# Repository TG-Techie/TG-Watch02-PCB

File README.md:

# TG-Watch02-PCB
---

## Description
Why buy an apple watch when you can spend your weekends building a microcontroller based "smart" watch instead? the TG-Watch is an open source, not-dumb watch meant for makers who want to hack on their watch or as great starting point to learn about programming.

Some of its features include:
- a 240x240, 1.54" lcd
- capacitive touchscreen
- USB Type-C port (2.0)
- Step counter and pedometer
- vibration motor and haptic motor driver
- Bluetooth 5, Bluetooth mesh, Thread, ZigBee

## Software
The TG-Watch was designed to run circuitpython, this gives anyone the flexibility to run what they can write. Additionally, there is on-going development for a python GUI framework (TG-Gui-4 and TG-Gui 5) that runs on the watch. This framework is intended to make writing UI programs to run on the fun and approachable. (Currently under going a re-write)

## Examples
Updates about software and hardware are often posted to twitter, [here](https://twitter.com/TG_Techie).

## What's on it?
- 2295018-2, USB Type-C Connector
- LSM6DSOX, accel & gyro
- DRV2605, Haptic motor driver
- NRF52840, MCU and BLE IC
- BQ27441, battery charge tracker IC
- DS3231, real time clock

## Contribution and Questions
If you have any questions feel free to reach out and start a discussion on twitter at `@TG_Techie` or on discord at `@TG-Techie#5402`.

## License

Design and copyright by Jonah Yolles-Murphy, 2020

Creative Commons Attribution/Share-Alike, all text above must be included in any redistribution. See license.txt for additional details.

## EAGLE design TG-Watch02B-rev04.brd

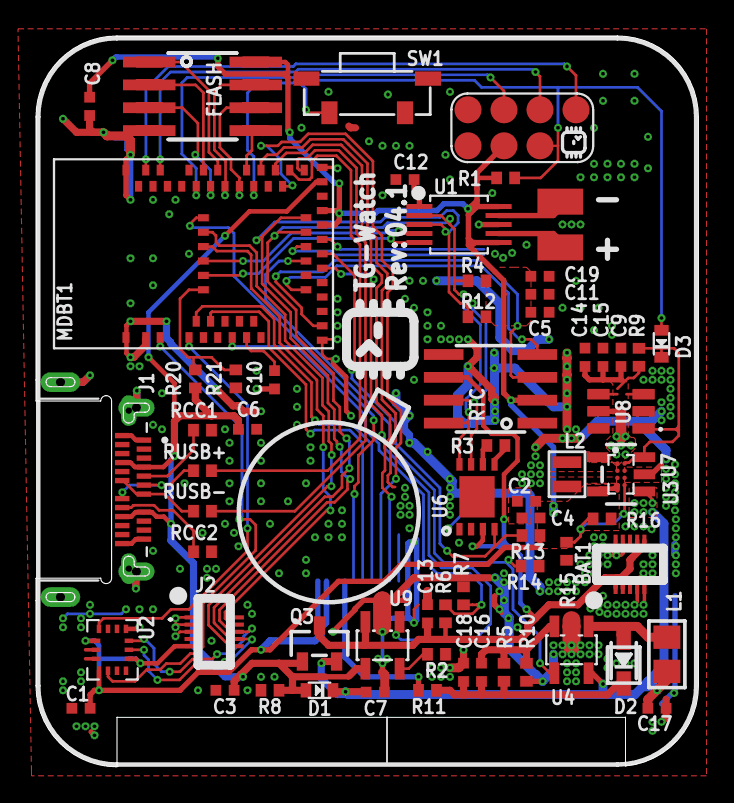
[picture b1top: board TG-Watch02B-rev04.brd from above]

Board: 2 copper layers, 36.8 x 40.6 mm, 66 parts (0 on the bottom side), 56 nets.

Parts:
04.1: TG-Watch; TG-PROD-LABEL-5MM
C1, C18: 4.7uf; MICROBUILDER__0402_NODIMS
C2, C3, C4, C5, C6, C7, C8, C9, C13, C14, C15, C17, C19: 10uf; MICROBUILDER__0402_NODIMS
C10: 0.1uF; MICROBUILDER__0402_NODIMS
C11, C12: 1uf; MICROBUILDER__0402_NODIMS
C16: 0.1nF; MICROBUILDER__0402_NODIMS
D1: NSR05T40XV2; SOD-523
D2: BAT54T1G; SOD-323
D3: BAS16XV2T1G; SOD-523
FLASH: W25Q128JVSIQ TR; SOIC8_208MIL
HEDR2: 1X02SMD; 1X2_SMD
IC3: W25Q128JVSIQ TR; SOIC8_150MIL
J1: USB-C-CON-TG_MOD-2295018-2.0; TG_RM_TE_2295018-2
J2: DISP_1.54_LCMTF15423A-C_LCD+CAPTCH_ASSEMBLY_DUALS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; TF-LCM15423A-C_DUALSIDE
J3: CON-BAT-TG-MEZ_FEMALE; MEZ-DF37NC-10DS
L1: 10uH; 0805
L2: 1uH - HMLQ20161B-1R0MDR; NONSTANDARD_INDUCTOR_5
MDBT1: MDBT50
Q3: DMG2305; SOT23-R
R1, R10, R13, R14: 10k; TG_0402
R2: 2k; TG_0402
R3: 11k; TG_0402
R4, R9, R12, R21: 100k; TG_0402
R5: 68k; TG_0402
R6: 270k; TG_0402
R7, R16: 330k; TG_0402
R8: 2.7K; TG_0402
R11: 220R; TG_0402
R15: 59k; TG_0402
R20: 51k; TG_0402
RCC1, RCC2: 5.1k; TG_0402
RTC: SEN-TIME-DS3231-(PERSICION-TEMP); SOIC8_150MIL
RUSB+: 22ohm; TG_0402
RUSB-: 22ohm; TG_0402
SW1: MICROBUILDER_SPST_TACTILE_RA_NO_ALIGN
U1: MICROBUILDER_PSOP10
U2: MICROBUILDER_LSM6DSOX; MICROBUILDER_LGA-14L
U3: VREG-TPS63036; TPS63036YFGR_BGA8N40P4X2_NOSILK
U4: FAN5331SX; SOT23-5@1
U5: MCP73831/OT; SOT23-5L
U6: LC709203F; WDFN8_3X4_0.65
U7: SOT23-5
U8: UNDERVOLT-TPS3702CX3; SOT95P280X110-6N
U$3: CON_SWD_POGO; SWD_POGO

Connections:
3V3: C1.2, C2.2, C4.2, C5.2, C8.2, C11.2, C19.2, FLASH.8, IC3.8, J2.FPC11, J2.FPC12, J2.MEZ5, MDBT1.28, MDBT1.30, R1.2, R4.2, R12.2, R13.1, R16.1, RTC.2, U1.6, U1.10, U2.5, U2.8, U2.12, U3.D1, U7.5, U$3.6
9.6V: C16.1, C18.1, D2.C, R5.2, R11.2
ACCEL_INT1: MDBT1.4, U2.4
ACCEL_INT2: MDBT1.3, U2.9
AREF: C10.2, MDBT1.12
BAT_CHRG_SET: R2.2, U5.5
CC1: J1.A5, RCC1.2
CC2: J1.B5, RCC2.2
D6_BACKLIGHT: MDBT1.23, R14.2, U4.4
D9_RTC_RESET: MDBT1.19, RTC.4
D10_RTC_INT: MDBT1.16, RTC.3
D11_CHRG_STAT: MDBT1.22, U5.1
D12_BAT_INT: MDBT1.24, R13.2, U6.4
D14_VBUS_PRESENT: MDBT1.56, R20.1, R21.2
D15_HAPTIC_ENABLE: MDBT1.57, U1.5
D16_HAPTIC_INT: MDBT1.58, U1.4
D17_CTP_INT: J2.MEZ9, MDBT1.59
D18_CTP_RESET: J2.MEZ6, MDBT1.60
D19_TFT_RESET: J2.FPC8, MDBT1.61
D20_TFT_DC: J2.FPC6, MDBT1.5
D22_TFT_CS: J2.FPC7, MDBT1.7
D+: MDBT1.35, RUSB+.1
D-: MDBT1.34, RUSB-.1
DRV_REG: C12.2, U1.1
GND: C1.1, C2.1, C3.1, C4.1, C5.1, C6.1, C7.1, C8.1, C9.2, C10.1, C11.1, C12.1, C13.1, C14.1, C15.1, C17.1, C18.2, C19.1, FLASH.4, IC3.4, J1.A1, J1.A12, J1.B1, J1.B12, J1.P1_1, J1.P1_2, J1.P2_1, J1.P2_2, J1.P4, J1.P5, J2.FPC1, J2.FPC2, J2.FPC10, J2.MEZ1, J2.MEZ2, J2.MEZ3, J3.P$4, J3.P$5, J3.P$9, J3.P$10, MDBT1.1, MDBT1.2, MDBT1.15, MDBT1.33, MDBT1.55, R2.1, R7.1, R8.1, R10.1, R14.1, R15.1, R21.1, RCC1.1, RCC2.1, RTC.5, SW1.1, U1.8, U2.1, U2.6, U2.7, U3.B2, U3.C2, U4.2, U5.2, U6.1, U6.2, U7.2, U8.2, U$3.1, U$3.5
HAPTIC+: HEDR2.1, U1.7
HAPTIC-: HEDR2.2, U1.9
L1: L2.1, U3.B1
L2: L2.2, U3.C1
MOSI: J2.FPC4, MDBT1.37
unnamed: C16.2, R5.1, R10.2, U4.3
unnamed: D2.A, L1.2, U4.1
QSPI_CS: FLASH.1, IC3.1, MDBT1.44
QSPI_DATA0: FLASH.5, IC3.5, MDBT1.41
QSPI_DATA1: FLASH.2, IC3.2, MDBT1.46
QSPI_DATA2: FLASH.3, IC3.3, MDBT1.45
QSPI_DATA3: FLASH.7, IC3.7, MDBT1.43
QSPI_SCK: FLASH.6, IC3.6, MDBT1.42
RESET: D3.A, MDBT1.40, R1.1, SW1.2, U$3.7
SCK: J2.FPC5, MDBT1.36
SCL: J2.MEZ7, MDBT1.27, R4.1, RTC.8, U1.2, U2.13, U6.8
SDA: J2.MEZ8, MDBT1.29, R12.1, RTC.7, U1.3, U2.14, U6.7
SENSE: R15.2, R16.2, U3.D2
SWDCLK: MDBT1.53, U$3.4
SWDIO: MDBT1.51, U$3.3
SWO: MDBT1.47, U$3.2
SYS_EN: D3.K, R9.1, U3.A2, U7.3, U8.1
TSENSE: R3.2, U6.6
TSW: R3.1, U6.5
USBD+: J1.A6, J1.B6, RUSB+.2
USBD-: J1.A7, J1.B7, RUSB-.2
VBAT: C13.2, J3.P$1, J3.P$2, J3.P$6, J3.P$7, Q3.3, R6.2, RTC.6, U5.3, U6.3
VBUS: C3.2, C6.2, D1.A, J1.A4, J1.A9, J1.B4, J1.B9, MDBT1.32, Q3.1, R8.2, R20.2, U5.4
VDIV: MDBT1.10, R6.1, R7.2
VLED: J2.FPC9, R11.1
VSORS: C7.2, C9.1, C14.2, C15.2, C17.2, D1.K, L1.1, Q3.2, R9.2, U3.A1, U4.5, U7.1, U8.3, U8.4, U8.5

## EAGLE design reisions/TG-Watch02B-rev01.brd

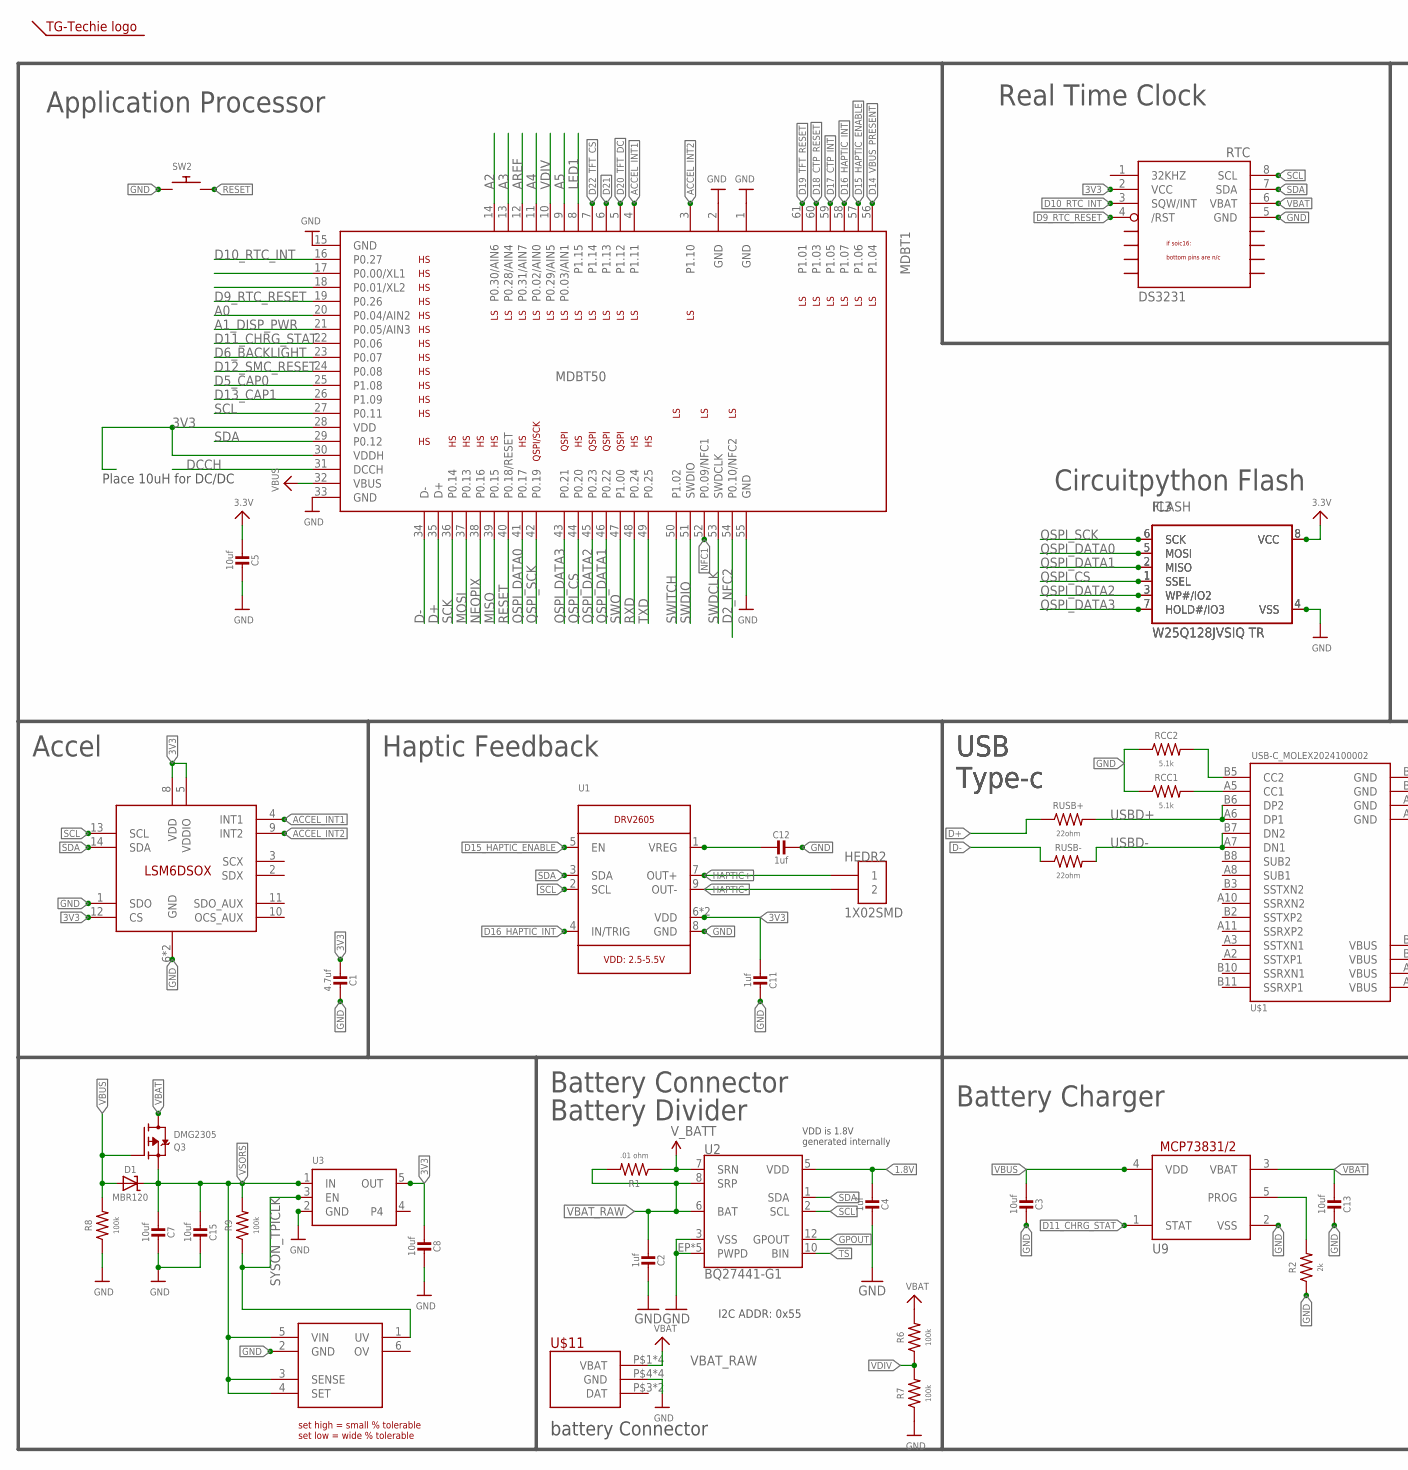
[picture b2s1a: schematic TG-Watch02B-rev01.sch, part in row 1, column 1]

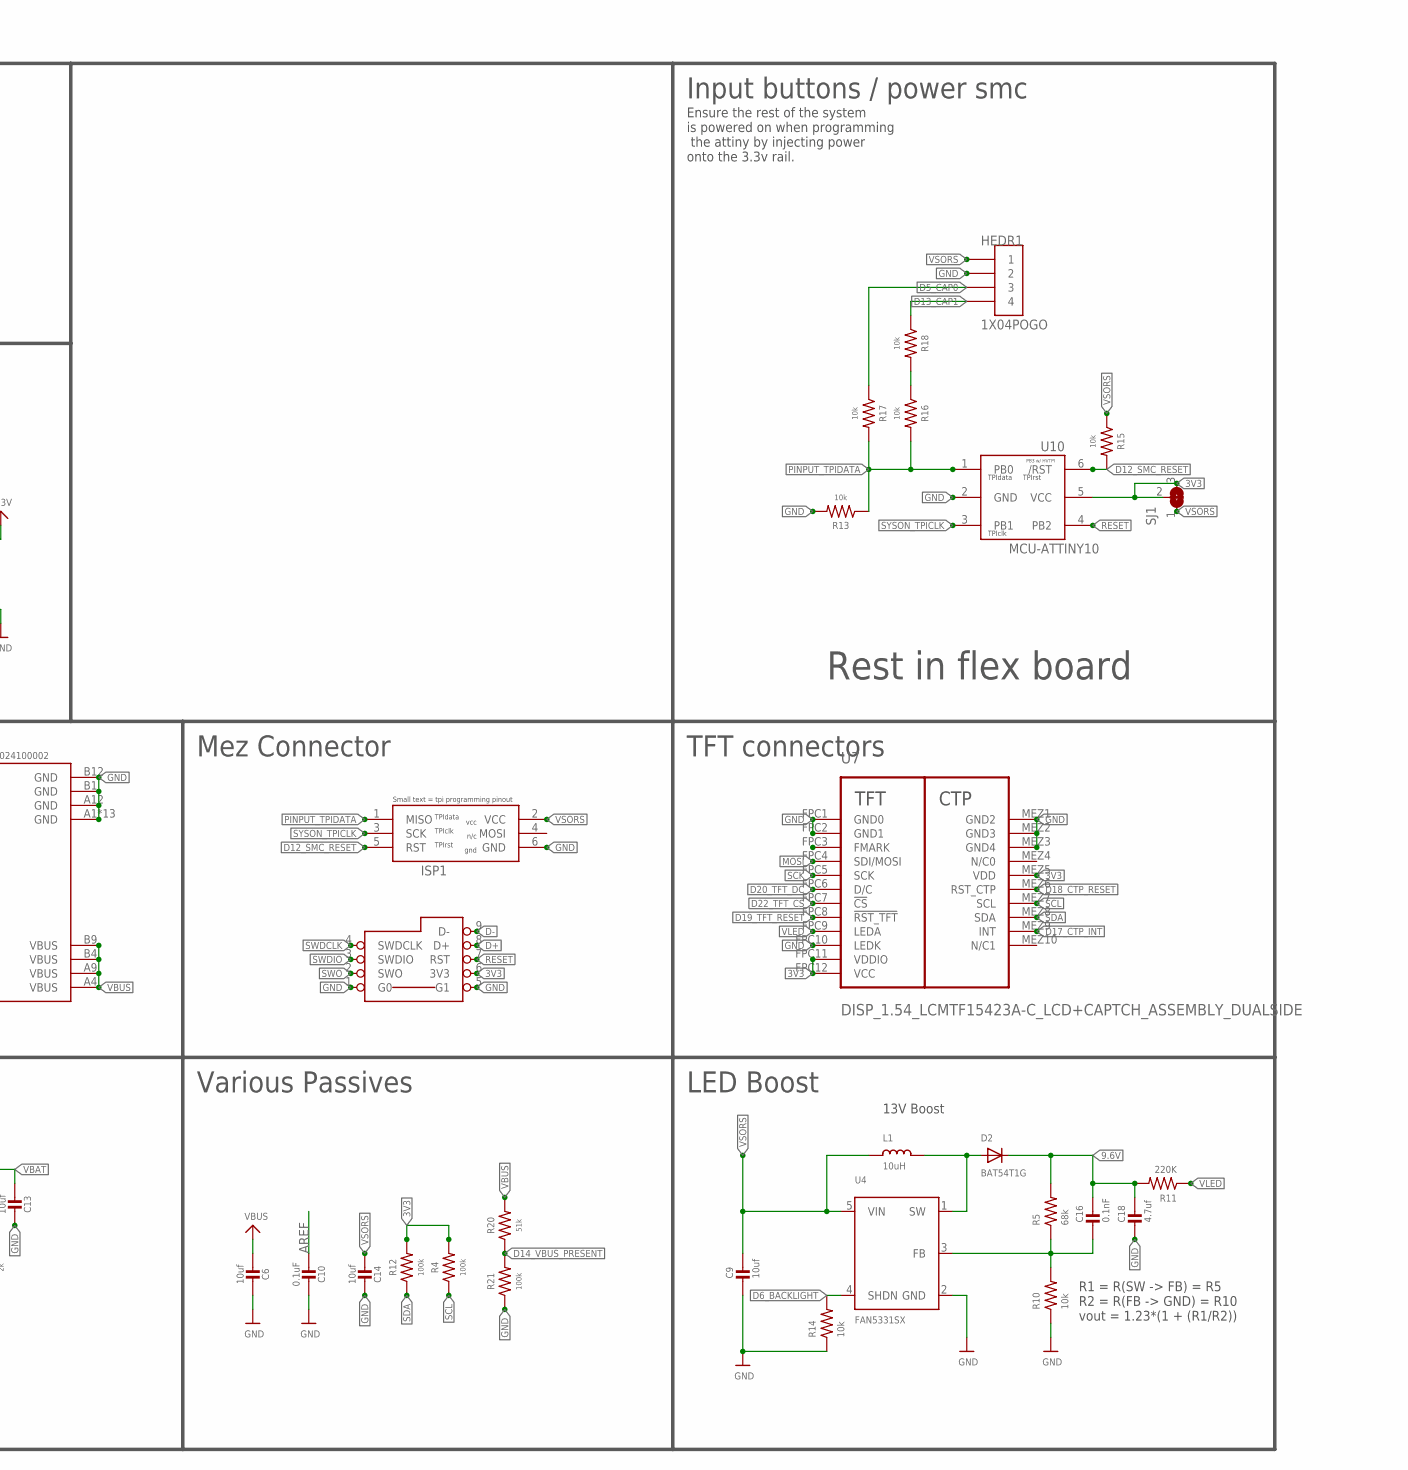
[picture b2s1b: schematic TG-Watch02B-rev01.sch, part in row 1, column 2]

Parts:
C1, C18: 4.7uf; MICROBUILDER__0402_NODIMS
C2, C4, C11, C12: 1uf; MICROBUILDER__0402_NODIMS
C3, C5, C6, C7, C8, C9, C13, C14, C15: 10uf; MICROBUILDER__0402_NODIMS
C10: 0.1uF; MICROBUILDER__0402_NODIMS
C16: 0.1nF; MICROBUILDER__0402_NODIMS
D1: MBR120; SOD-523
D2: BAT54T1G; SOD-523
FLASH: W25Q128JVSIQ TR; SOIC8_208MIL
HEDR1: 1X04POGO; 1X4_POGO
HEDR2: 1X02SMD; 1X2_SMD
IC3: W25Q128JVSIQ TR; SOIC8_150MIL
ISP1: CON-ICSP/ISP-AVR-POGO; 2X3_POGO_AVR
L1: 10uH; 0805
MDBT1: MDBT50
Q3: DMG2305; SOT23-R
R1: .01 ohm; TG_0402
R2: 2k; TG_0402
R4, R6, R7, R8, R9, R12, R21: 100k; TG_0402
R5: 68k; TG_0402
R10, R13, R14, R15, R16, R17, R18: 10k; TG_0402
R11: 220K; TG_0402
R20: 51k; TG_0402
RCC1, RCC2: 5.1k; TG_0402
RTC: SEN-TIME-DS3231-(PERSICION-TEMP); SOIC8_150MIL
RUSB+: 22ohm; TG_0402
RUSB-: 22ohm; TG_0402
SJ1: JUMPER_OPEN_2_OP; SOLDERJUMPER_2WAY_OPEN_NOPASTE
SW2: SWITCH_PUSHBUTTONC&K_KSS; BTN_CK_KSS
U1: HAPTIC_DRIVER_DRV2605_SOP; MICROBUILDER_PSOP10
U2: BQ27441-G1; PDSO-N12
U3: VREG_STD_MIN_SOT23-5; SOT23-5
U4: FAN5331SX; SOT23-5@1
U7: DISP_1.54_LCMTF15423A-C_LCD+CAPTCH_ASSEMBLY_DUALS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; TF-LCM15423A-C_DUALSIDE
U8: UNDERVOLT-TPS3702CX3; SOT95P280X110-6N
U9: MCP73831/OT; SOT23-5L
U10: MCU-ATTINY10; SOT23-6
U$1: USB-C_MOLEX2024100002; USB-C_2024100002_MOLEX
U$3: MICROBUILDER_LSM6DSOX; MICROBUILDER_LGA-14L
U$11: CON-BAT-TG-MEZ_FEMALE; MEZ-DF37NC-10DS
U$13: CON_SWD_POGO_USB; SWD_POGO_USB
U$14: LOGO-TG-TECHIE5MM-SYMB; TG-LOGO-5MM-SYMB

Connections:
1.8V: C4.2, U2.5 (VDD)
3V3: C1.2, C5.2, C8.2, C11.2, FLASH.8 (VCC), IC3.8 (VCC), MDBT1.28 (VDD), MDBT1.30 (VDDH), R4.2, R12.2, RTC.2 (VCC), SJ1.2, SJ1.3, U1.6 (VDD), U1.10 (VDD), U3.5 (OUT), U7.FPC11 (VDDIO), U7.FPC12 (VCC), U7.MEZ5 (VDD), U10.5 (VCC), U$3.5 (VDDIO), U$3.8 (VDD), U$3.12 (CS), U$13.6 (3V3)
9.6V: C16.1, C18.1, D2.K (C), R5.2, R11.2
A0: MDBT1.20 (P0.04/AIN2)
A1_DISP_PWR: MDBT1.21 (P0.05/AIN3)
A2: MDBT1.14 (P0.30/AIN6)
A3: MDBT1.13 (P0.28/AIN4)
A4: MDBT1.11 (P0.02/AIN0)
A5: MDBT1.9 (P0.03/AIN1)
ACCEL_INT1: MDBT1.4 (P1.11), U$3.4 (INT1)
ACCEL_INT2: MDBT1.3 (P1.10), U$3.9 (INT2)
AREF: C10.2, MDBT1.12 (P0.31/AIN7)
BAT_CHRG_SET: R2.2, U9.5 (PROG)
CC1: RCC1.2, U$1.A5 (CC1)
CC2: RCC2.2, U$1.B5 (CC2)
D2_NFC2: MDBT1.54 (P0.10/NFC2)
D5_CAP0: HEDR1.3, MDBT1.25 (P1.08), R17.1
D6_BACKLIGHT: MDBT1.23 (P0.07), R14.2, U4.4 (SHDN)
D9_RTC_RESET: MDBT1.19 (P0.26), RTC.4 (/RST)
D10_RTC_INT: MDBT1.16 (P0.27), RTC.3 (SQW/INT)
D11_CHRG_STAT: MDBT1.22 (P0.06), U9.1 (STAT)
D12_SMC_RESET: ISP1.5 (RST), MDBT1.24 (P0.08), R15.2, U10.6 (/RST)
D13_CAP1: HEDR1.4, MDBT1.26 (P1.09), R18.1
D14_VBUS_PRESENT: MDBT1.56 (P1.04), R20.1, R21.2
D15_HAPTIC_ENABLE: MDBT1.57 (P1.06), U1.5 (EN)
D16_HAPTIC_INT: MDBT1.58 (P1.07), U1.4 (IN/TRIG)
D17_CTP_INT: MDBT1.59 (P1.05), U7.MEZ9 (INT)
D18_CTP_RESET: MDBT1.60 (P1.03), U7.MEZ6 (RST_CTP)
D19_TFT_RESET: MDBT1.61 (P1.01), U7.FPC8 (!RST_TFT)
D20_TFT_DC: MDBT1.5 (P1.12), U7.FPC6 (D/C)
D21: MDBT1.6 (P1.13)
D22_TFT_CS: MDBT1.7 (P1.14), U7.FPC7 (!CS)
D+: MDBT1.35 (D+), RUSB+.1, U$13.8 (D+)
D-: MDBT1.34 (D-), RUSB-.1, U$13.9 (D-)
DCCH: MDBT1.31 (DCCH)
DRV_REG: C12.2, U1.1 (VREG)
GND: C1.1, C2.1, C3.1, C4.1, C5.1, C6.1, C7.1, C8.1, C9.2, C10.1, C11.1, C12.1, C13.1, C14.1, C15.1, C18.2, FLASH.4 (VSS), HEDR1.2, IC3.4 (VSS), ISP1.6 (GND), MDBT1.1 (GND), MDBT1.2 (GND), MDBT1.15 (GND), MDBT1.33 (GND), MDBT1.55 (GND), R2.1, R7.1, R8.1, R10.1, R13.2, R14.1, R21.1, RCC1.1, RCC2.1, RTC.5 (GND), SW2.P$1, U1.8 (GND), U2.3 (VSS), U2.EP (PWPD), U2.EP1 (PWPD), U2.EP2 (PWPD), U2.EP3 (PWPD), U2.EP4 (PWPD), U3.2 (GND), U4.2 (GND), U7.FPC1 (GND0), U7.FPC2 (GND1), U7.FPC10 (LEDK), U7.MEZ1 (GND2), U7.MEZ2 (GND3), U7.MEZ3 (GND4), U8.2 (GND), U9.2 (VSS), U10.2 (GND), U$1.A1 (GND), U$1.A12 (GND), U$1.B1 (GND), U$1.B12 (GND), U$1.P$1 (GND), U$1.P$2 (GND), U$1.P$3 (GND), U$1.P$4 (GND), U$1.P$5 (GND), U$1.P$6 (GND), U$1.P$7 (GND), U$1.P$8 (GND), U$1.SHLD0 (GND), U$1.SHLD1 (GND), U$1.SHLD2 (GND), U$1.SHLD3 (GND), U$3.1 (SDO), U$3.6 (GND), U$3.7 (GND), U$11.P$4 (GND), U$11.P$5 (GND), U$11.P$9 (GND), U$11.P$10 (GND), U$13.1 (G0), U$13.5 (G1)
GPOUT: U2.12 (GPOUT)
HAPTIC+: HEDR2.1, U1.7 (OUT+)
HAPTIC-: HEDR2.2, U1.9 (OUT-)
LED1: MDBT1.8 (P1.15)
MISO: MDBT1.39 (P0.15)
MOSI: MDBT1.37 (P0.13), U7.FPC4 (SDI/MOSI)
unnamed: C16.2, R5.1, R10.2, U4.3 (FB)
unnamed: D2.A, L1.2, U4.1 (SW)
unnamed: R16.1, R18.2
NEOPIX: MDBT1.38 (P0.16)
NFC1: MDBT1.52 (P0.09/NFC1)
PINPUT_TPIDATA: ISP1.1 (MISO), R13.1, R16.2, R17.2, U10.1 (PB0)
QSPI_CS: FLASH.1 (SSEL), IC3.1 (SSEL), MDBT1.44 (P0.20)
QSPI_DATA0: FLASH.5 (MOSI), IC3.5 (MOSI), MDBT1.41 (P0.17)
QSPI_DATA1: FLASH.2 (MISO), IC3.2 (MISO), MDBT1.46 (P0.22)
QSPI_DATA2: FLASH.3 (WP#/IO2), IC3.3 (WP#/IO2), MDBT1.45 (P0.23)
QSPI_DATA3: FLASH.7 (HOLD#/IO3), IC3.7 (HOLD#/IO3), MDBT1.43 (P0.21)
QSPI_SCK: FLASH.6 (SCK), IC3.6 (SCK), MDBT1.42 (P0.19)
RESET: MDBT1.40 (P0.18/RESET), SW2.P$2, U10.4 (PB2), U$13.7 (RST)
RXD: MDBT1.48 (P0.24)
SCK: MDBT1.36 (P0.14), U7.FPC5 (SCK)
SCL: MDBT1.27 (P0.11), R4.1, RTC.8 (SCL), U1.2 (SCL), U2.2 (SCL), U7.MEZ7 (SCL), U$3.13 (SCL)
SDA: MDBT1.29 (P0.12), R12.1, RTC.7 (SDA), U1.3 (SDA), U2.1 (SDA), U7.MEZ8 (SDA), U$3.14 (SDA)
SWDCLK: MDBT1.53 (SWDCLK), U$13.4 (SWDCLK)
SWDIO: MDBT1.51 (SWDIO), U$13.3 (SWDIO)
SWITCH: MDBT1.50 (P1.02)
SWO: MDBT1.47 (P1.00), U$13.2 (SWO)
SYSON_TPICLK: ISP1.3 (SCK), R9.1, U3.3 (EN), U8.1 (UV), U10.3 (PB1)
TS: U2.10 (BIN)
TXD: MDBT1.49 (P0.25)
USBD+: RUSB+.2, U$1.A6 (DP1), U$1.B6 (DP2)
USBD-: RUSB-.2, U$1.A7 (DN1), U$1.B7 (DN2)
VBAT: C13.2, Q3.3 (D), R1.1, R6.2, RTC.6 (VBAT), U2.7 (SRN), U9.3 (VBAT)
VBAT_RAW: C2.2, R1.2, U2.6 (BAT), U2.8 (SRP), U$11.P$1 (VBAT), U$11.P$2 (VBAT), U$11.P$6 (VBAT), U$11.P$7 (VBAT)
VBUS: C3.2, C6.2, D1.A, MDBT1.32 (VBUS), Q3.1 (G), R8.2, R20.2, U9.4 (VDD), U$1.A4 (VBUS), U$1.A9 (VBUS), U$1.B4 (VBUS), U$1.B9 (VBUS)
VDIV: MDBT1.10 (P0.29/AIN5), R6.1, R7.2
VLED: R11.1, U7.FPC9 (LEDA)
VSORS: C7.2, C9.1, C14.2, C15.2, D1.K (C), HEDR1.1, ISP1.2 (VCC), L1.1, Q3.2 (S), R9.2, R15.1, SJ1.1, U3.1 (IN), U4.5 (VIN), U8.3 (SENSE), U8.4 (SET), U8.5 (VIN)

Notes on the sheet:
Place 10uH for DC/DC
13V Boost
R1 = R(SW -> FB) = R5 R2 = R(FB -> GND) = R10 vout = 1.23*(1 + (R1/R2))
battery Connector
Battery Connector
Battery Divider
Battery Charger
Various Passives
Mez Connector
TFT connectors
LED Boost
USB Type-c
Haptic Feedback
Accel
Circuitpython Flash
Input buttons / power smc
Application Processor
Ensure the rest of the system is powered on when programming the attiny by injecting power onto the 3.3v rail.
Rest in flex board
Real Time Clock
VDD is 1.8V generated internally
I2C ADDR: 0x55

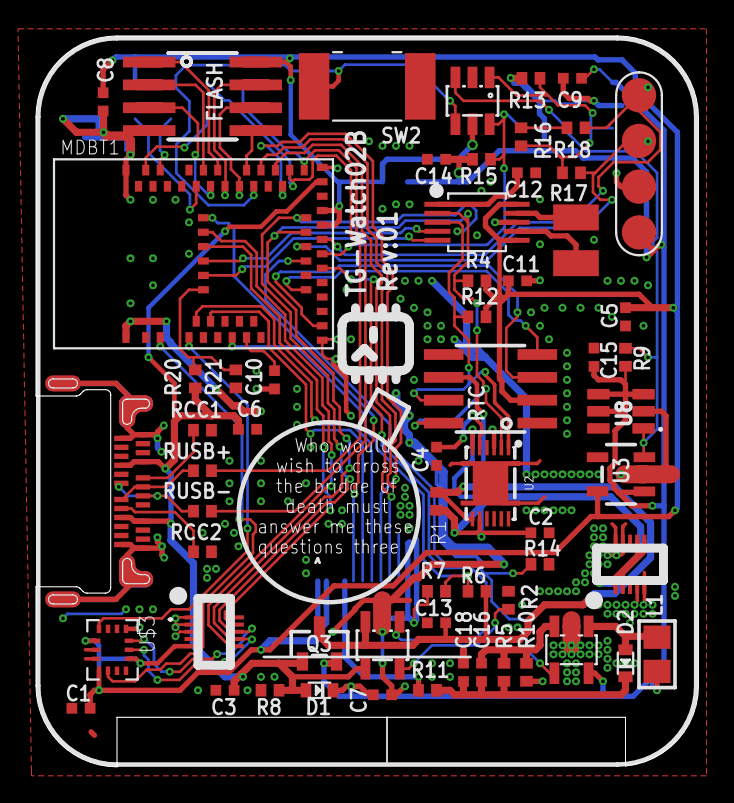
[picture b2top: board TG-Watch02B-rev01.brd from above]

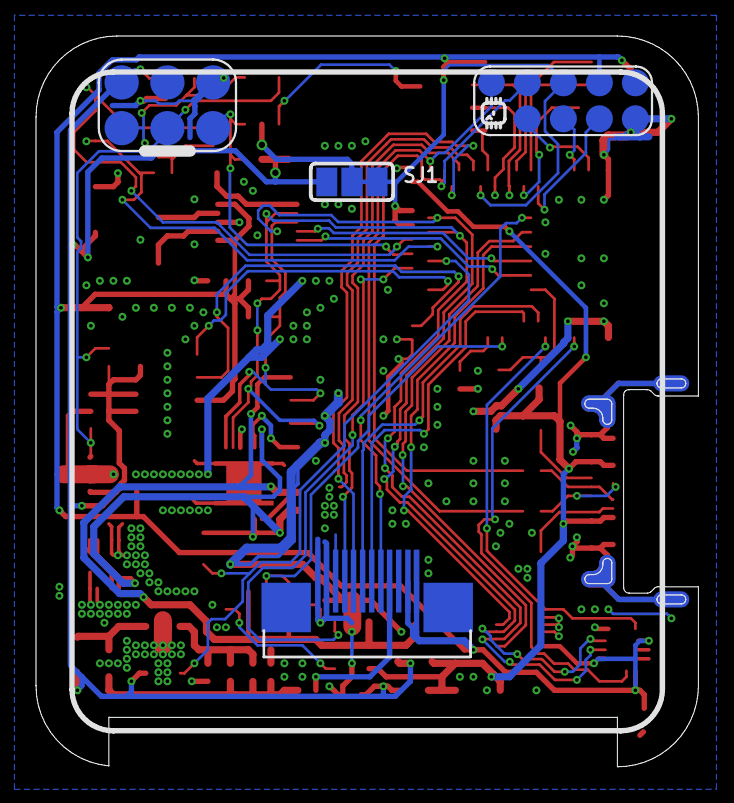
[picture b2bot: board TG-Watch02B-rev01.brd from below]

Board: 2 copper layers, 36.8 x 40.6 mm, 66 parts (3 on the bottom side), 57 nets.

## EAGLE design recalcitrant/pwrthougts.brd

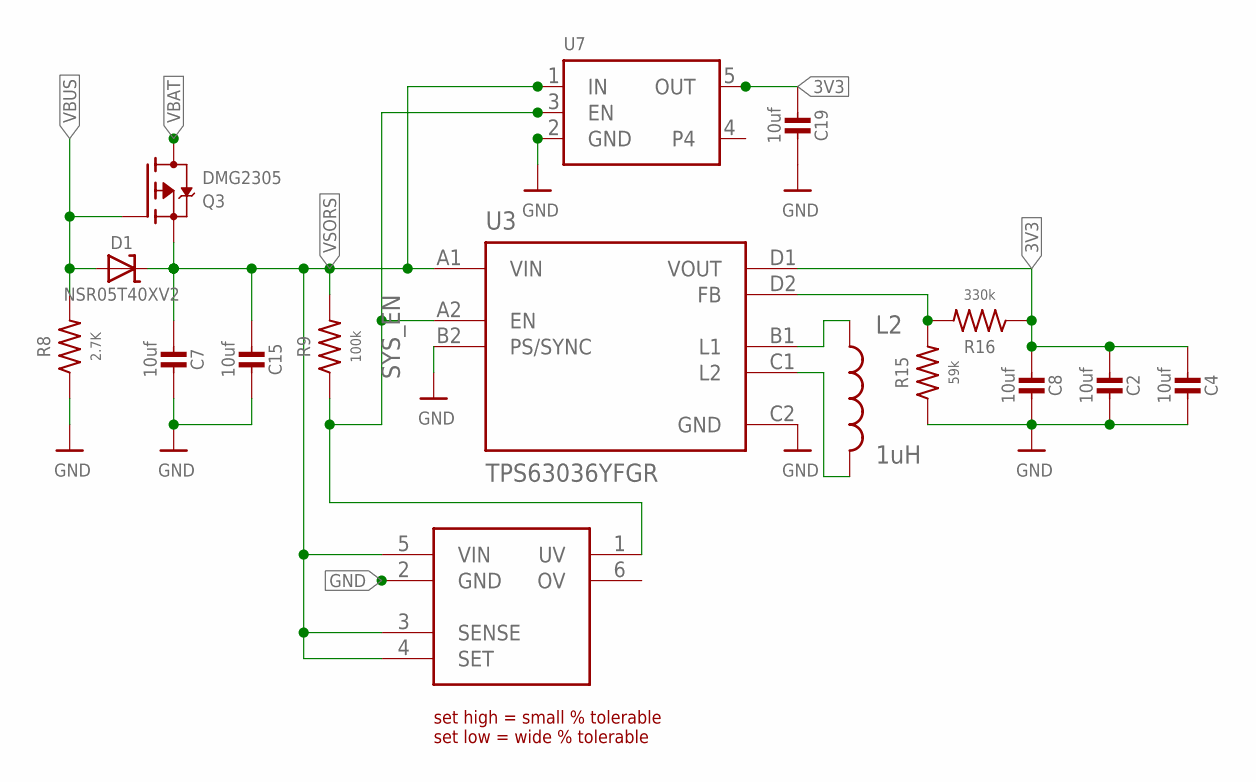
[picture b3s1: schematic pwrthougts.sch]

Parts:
C2, C4, C7, C8, C15, C19: 10uf; MICROBUILDER__0402_NODIMS
D1: NSR05T40XV2; SOD-523
L2: 1uH; NONSTANDARD_INDUCTOR_5
Q3: DMG2305; SOT23-R
R8: 2.7K; TG_0402
R9: 100k; TG_0402
R15: 59k; TG_0402
R16: 330k; TG_0402
U3: TPS63036YFGR; BGA8N40P4X2_181X107X62N
U7: VREG_STD_MIN_SOT23-5; SOT23-5
U8: UNDERVOLT-TPS3702CX3; SOT95P280X110-6N

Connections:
3V3: C2.2, C4.2, C8.2, C19.2, R16.1, U3.D1 (VOUT), U7.5 (OUT)
GND: C2.1, C4.1, C7.1, C8.1, C15.1, C19.1, R8.1, R15.1, U3.B2 (PS/SYNC), U3.C2 (GND), U7.2 (GND), U8.2 (GND)
L1: L2.1, U3.B1 (L1)
L2: L2.2, U3.C1 (L2)
SENSE: R15.2, R16.2, U3.D2 (FB)
SYS_EN: R9.1, U3.A2 (EN), U7.3 (EN), U8.1 (UV)
VBAT: Q3.3 (D)
VBUS: D1.A, Q3.1 (G), R8.2
VSORS: C7.2, C15.2, D1.K (C), Q3.2 (S), R9.2, U3.A1 (VIN), U7.1 (IN), U8.3 (SENSE), U8.4 (SET), U8.5 (VIN)

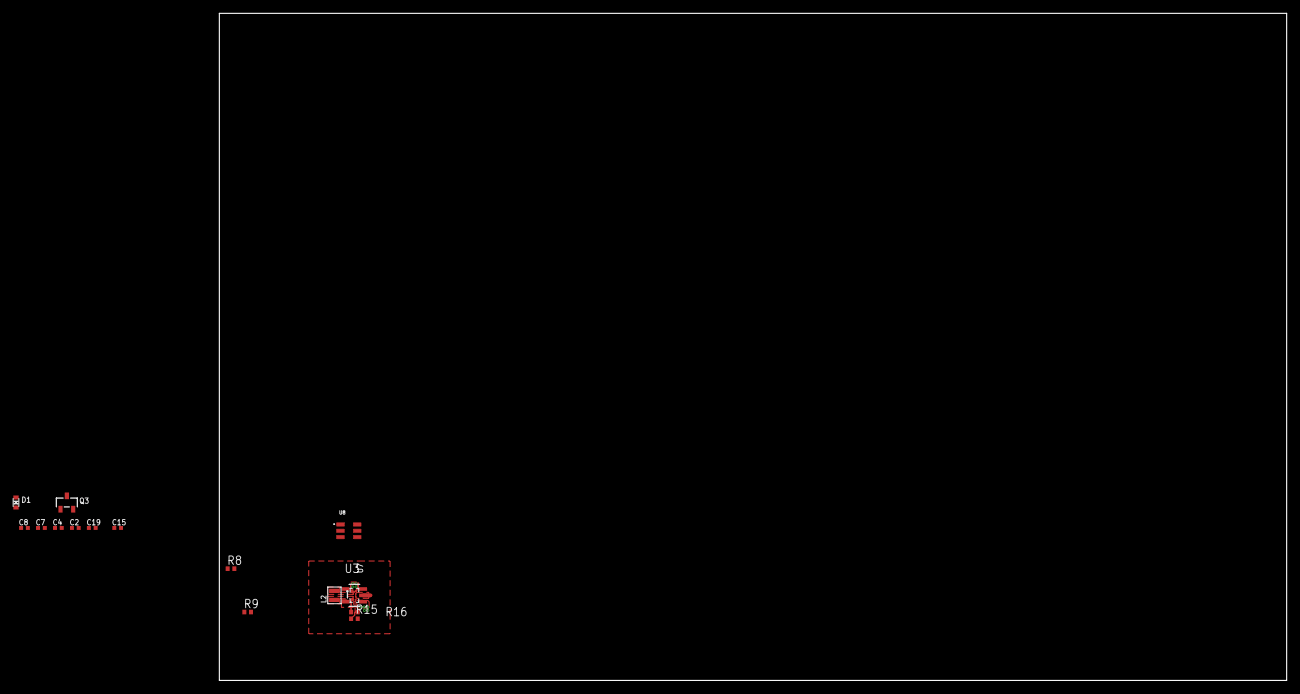
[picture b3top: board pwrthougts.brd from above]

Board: 2 copper layers, 160.0 x 100.0 mm, 16 parts (0 on the bottom side), 8 nets.

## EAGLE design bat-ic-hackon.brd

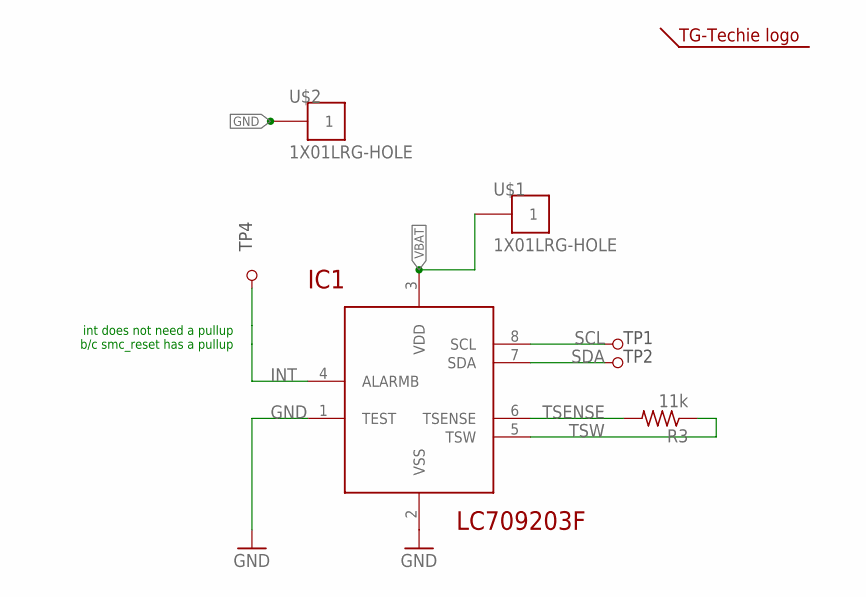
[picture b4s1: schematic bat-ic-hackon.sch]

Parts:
IC1: LC709203F; WDFN8_3X4_0.65
R3: 11k; TG_0402
TP1, TP2, TP4: TESTPOINT_1X1_SMALL; 1X1_POGO_SMALL
U$1, U$2: 1X01LRG-HOLE; 1X1_HOLE_LRG
U$3: LOGO-TG-TECHIE5MM-SYMB; TG-LOGO-5MM-SYMB

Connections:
GND: IC1.1 (TEST), IC1.2 (VSS), U$2.1
INT: IC1.4 (ALARMB), TP4.1
SCL: IC1.8 (SCL), TP1.1
SDA: IC1.7 (SDA), TP2.1
TSENSE: IC1.6 (TSENSE), R3.2
TSW: IC1.5 (TSW), R3.1
VBAT: IC1.3 (VDD), U$1.1

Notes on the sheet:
int does not need a pullup b/c smc_reset has a pullup

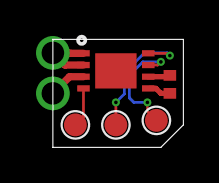
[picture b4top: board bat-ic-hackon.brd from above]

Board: 2 copper layers, 7.2 x 6.0 mm, 8 parts (1 on the bottom side), 7 nets.

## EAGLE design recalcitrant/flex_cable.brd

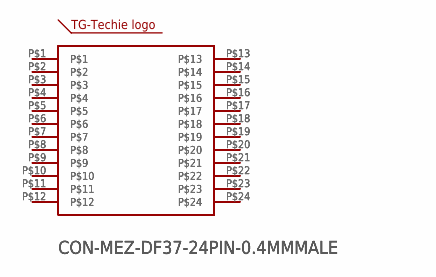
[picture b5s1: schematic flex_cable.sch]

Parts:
U$1, U$11: CON-MEZ-DF37-24PIN-0.4MMMALE; MEZ-DF37B-24DP
U$2: LOGO-TG-TECHIE5MM; TG-LOGO-5MM

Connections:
unnamed: U$1.P$1, U$11.P$1
unnamed: U$1.P$2, U$11.P$2
unnamed: U$1.P$3, U$11.P$3
unnamed: U$1.P$4, U$11.P$4
unnamed: U$1.P$5, U$11.P$5
unnamed: U$1.P$6, U$11.P$6
unnamed: U$1.P$7, U$11.P$7
unnamed: U$1.P$8, U$11.P$8
unnamed: U$1.P$9, U$11.P$9
unnamed: U$1.P$10, U$11.P$10
unnamed: U$1.P$11, U$11.P$11
unnamed: U$1.P$12, U$11.P$12
unnamed: U$1.P$13, U$11.P$13
unnamed: U$1.P$14, U$11.P$14
unnamed: U$1.P$15, U$11.P$15
unnamed: U$1.P$16, U$11.P$16
unnamed: U$1.P$17, U$11.P$17
unnamed: U$1.P$18, U$11.P$18
unnamed: U$1.P$19, U$11.P$19
unnamed: U$1.P$20, U$11.P$20
unnamed: U$1.P$21, U$11.P$21
unnamed: U$1.P$22, U$11.P$22
unnamed: U$1.P$23, U$11.P$23
unnamed: U$1.P$24, U$11.P$24

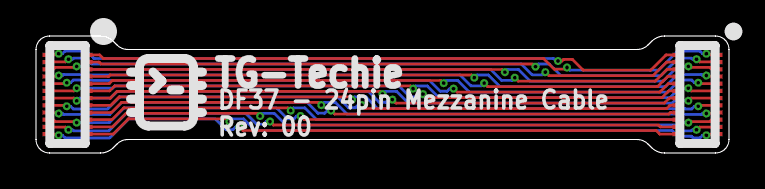
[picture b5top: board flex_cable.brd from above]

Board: 2 copper layers, 38.5 x 6.5 mm, 3 parts (0 on the bottom side), 24 nets.

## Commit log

2020-09-21 init commit
2020-09-21 readme correction and additions
2021-01-14 chagne battery IC and make path for rev02 boards
2021-03-03 pre-order
2022-07-07 2022jul07

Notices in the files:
parts and their libraries:
microbuilder: This work is placed in the public domain, and may be freely used for commercial and non-commercial work with the following conditions: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
SparkFun-Aesthetics: Licensing: Creative Commons ShareAlike 4.0 International - https://creativecommons.org/licenses/by-sa/4.0
